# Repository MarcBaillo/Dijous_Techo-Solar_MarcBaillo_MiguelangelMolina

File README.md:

## Dijous_Techo-Solar_MarcBaillo_MiguelangelMolina
Proyecto de Herramientas de Diseño del Techo Solar (Jueves).

# Autores
- Miguelangel Molina(@MiaMoSaN)
- Marc Baillo (@MarcBaillo)

## Objectivos del proyecto

El objetivo que tenemos es conseguir diseñar un techo solar que estara formado por un microcontrolador, 2 motores que controlaran la apertura con final de carrera y el movimiento de la cortina, un sensor que evite atrapamientos y una luz ambiental producida por un LED RGB. Todo esto estara implementado en una PCB, pasando por las fases de diagrama de bloque, que luego pasar al esquematico y alfinal al layout, para luego evaluarlo y hacer unos presupuestos de cuanto valdra crear la placa.

## Requisitos i especificaciones:

- Diseño integral de un techo solar controlado por microcontrolador.
- Implementación de un motor de apertura con final de carrera.
- Integración de un motor de la cortina.
- Luz ambiental RGB.
- Integración de un sensor digital para evitar que atrapamientos.

## Diagrama de bloque

## Tabla de componentes
| Descripción        | Manufacturer Number          | Descripción | Datasheet          | Proveidor        | Unidades       | Precio Unitario |
|:----------------:|:-------------------------:|:----------------:|:---------------:|:--------------:|:--------------:|:--------------:|
| Microcontrolador | PIC18LF2580-I/SO | Procesador que actúa como cerebro de control del circuito | [Datasheet](https://ww1.microchip.com/downloads/aemDocuments/documents/OTH/ProductDocuments/DataSheets/39637d.pdf) | DigiKey | 1 | 9,2€ |
| Regulador de tensión | LM1117DT-3.3/NOPB  | Dispositivo que hace que la tensión de entrada pase de 12V a los que necesita el microcontrolador (3,3V) | [Datasheet](https://www.ti.com/lit/ds/symlink/lm1117.pdf?ts=1710745623625&ref_url=https%253A%252F%252Fwww.mouser.se%252F) | Mouser Electronics | 1 | 1,61€ |
| Conector | DB9  | Se ocupa de la conexión entre diferentes dispositivos |[Datasheet](https://www.mouser.es/datasheet/2/18/1/Cable_Glands_and_Cord_Grips-806485.pdf) | Mouser Electronics | 1 | 19,08€ |
| Oscilador | ECS-80-8-30-JGN-TR | Genera ondas de señales precisas| [Datasheet](https://www.mouser.es/datasheet/2/122/ecx_53r-1775695.pdf) | Mouser Electronics | 1 | 0,53€ |
| H-Driver | DRV8231ADDAR  | controla el sentido de giro de un motor | [Datasheet](https://www.ti.com/lit/ds/symlink/drv8231a.pdf?ts=1710753914026&ref_url=https%253A%252F%252Fwww.mouser.de%252F) | Mouser Electronics | 1 | 1,24€ |
| Transceiver | 	TCAN332DR  | Dispositivo que recibe y trtransmite datos |[Datasheet](https://www.ti.com/lit/ds/symlink/tcan332g.pdf?ts=1710924087476&ref_url=https%253A%252F%252Fwww.mouser.de%252F) | DigiKey | 1 | 2,83€ |
| LED RGB | LB Q39G-N1OO-35-1-5-R18  | LED que da luz ambiental al coche |[Datasheet](https://look.ams-osram.com/m/6e36864d019f51d4/original/LB-Q39G.pdf) | DigiKey | 1 | 0,2€ |
| Motor | D4387-12-ME  | Motores para poder abrir y cerrar el cristal o la cortina del techo | [Datasheet](https://transmotec.es/Download/Catalog/Transmotec-EN-DC-12W-450W-2022.pdf) | Transmotec | 2 | 345€ |
| Switch | SS-01GPD  | Dispositivos que controlan cuando es el final de carrera | [Datasheet](https://www.mouser.es/datasheet/2/307/en_ss-1509069.pdf) | Mouser Electronics | 1 | 1,27€ |
| Pulsador | MPB01-1B00-S-D  | Dispositivo que permite controlar el motor para que el techo o cortina se abra o se cierre  | [Datasheet](https://www.mouser.es/datasheet/2/670/mpb01-2474754.pdf) | Mouser Electronics | 2 | 3,14€ |
| Conector | ICSP  | Sirve para comunicarse con el exterior para programar el microcontrolador | [Datasheet](https://ww1.microchip.com/downloads/en/DeviceDoc/30277d.pdf) | DigiKey | 2 | 1,52€ |

## Historial de canvis 

| Data | Autor | Descripció |
|:------:|:------:|:------------:|
| 20-03-2025 | Marc y Miguel | Creado el proyecto y escogido el diseño que se trabajara (Techo Solar) |
| 20-03-2025 | Marc y Miguel | Elección de componentes y presentación del proyecto (Sesión 1) |
| 20-03-2025 | Marc y Miguel | Creación de Diagrama de Bloque |
| 23-03-2025 | Marc | Cadlab y GitHub creado |
| 24-03-2025 | Miguel | Creación del Esquematico |
| 25-03-2025 | Marc | Simulaciones hechas |
| 26-03-2025 | Miguel | Modificación Diagrama de Bloque |
| 27-03-2025 | Marc | Creació del README |
| 27-03-2025 | Marc y Miguel | Modificación presentación proyecto (Sesión 2) |
| 31-03-2025 | Miguel | Creación Layout |
| 02-04-2025 | Marc | Simulación ADC hecha |
| 03-04-2025 | Miguel y Marc | Modificación presentación proyecto (Sesión 3) |
| 03-04-2025 | Miguel | Corrección errores Layout y Esquematicos |
| 09-04-2025 | Marc | Modificación Layout (acabar de poner vista 3D y packages bien) |
| 09-04-2025 | Marc |  Modificación presentación proyecto (Sesión 4)  |
| 10-04-2025 | Marc y Miguel |  Modificación presentación proyecto (Sesión 4)  |
| 10-04-2025 | Miguel | Finalización del Esquematico y del Layout |
| 10-04-2025 | Miguel | Reglas de diseño definidas |
| 23-04-2025 | Marc | Presupuesto hecho |
| 24-04-2025 | Miguel y Marc | Modificación presentación proyecto (Sesión presentación proyecto final) |

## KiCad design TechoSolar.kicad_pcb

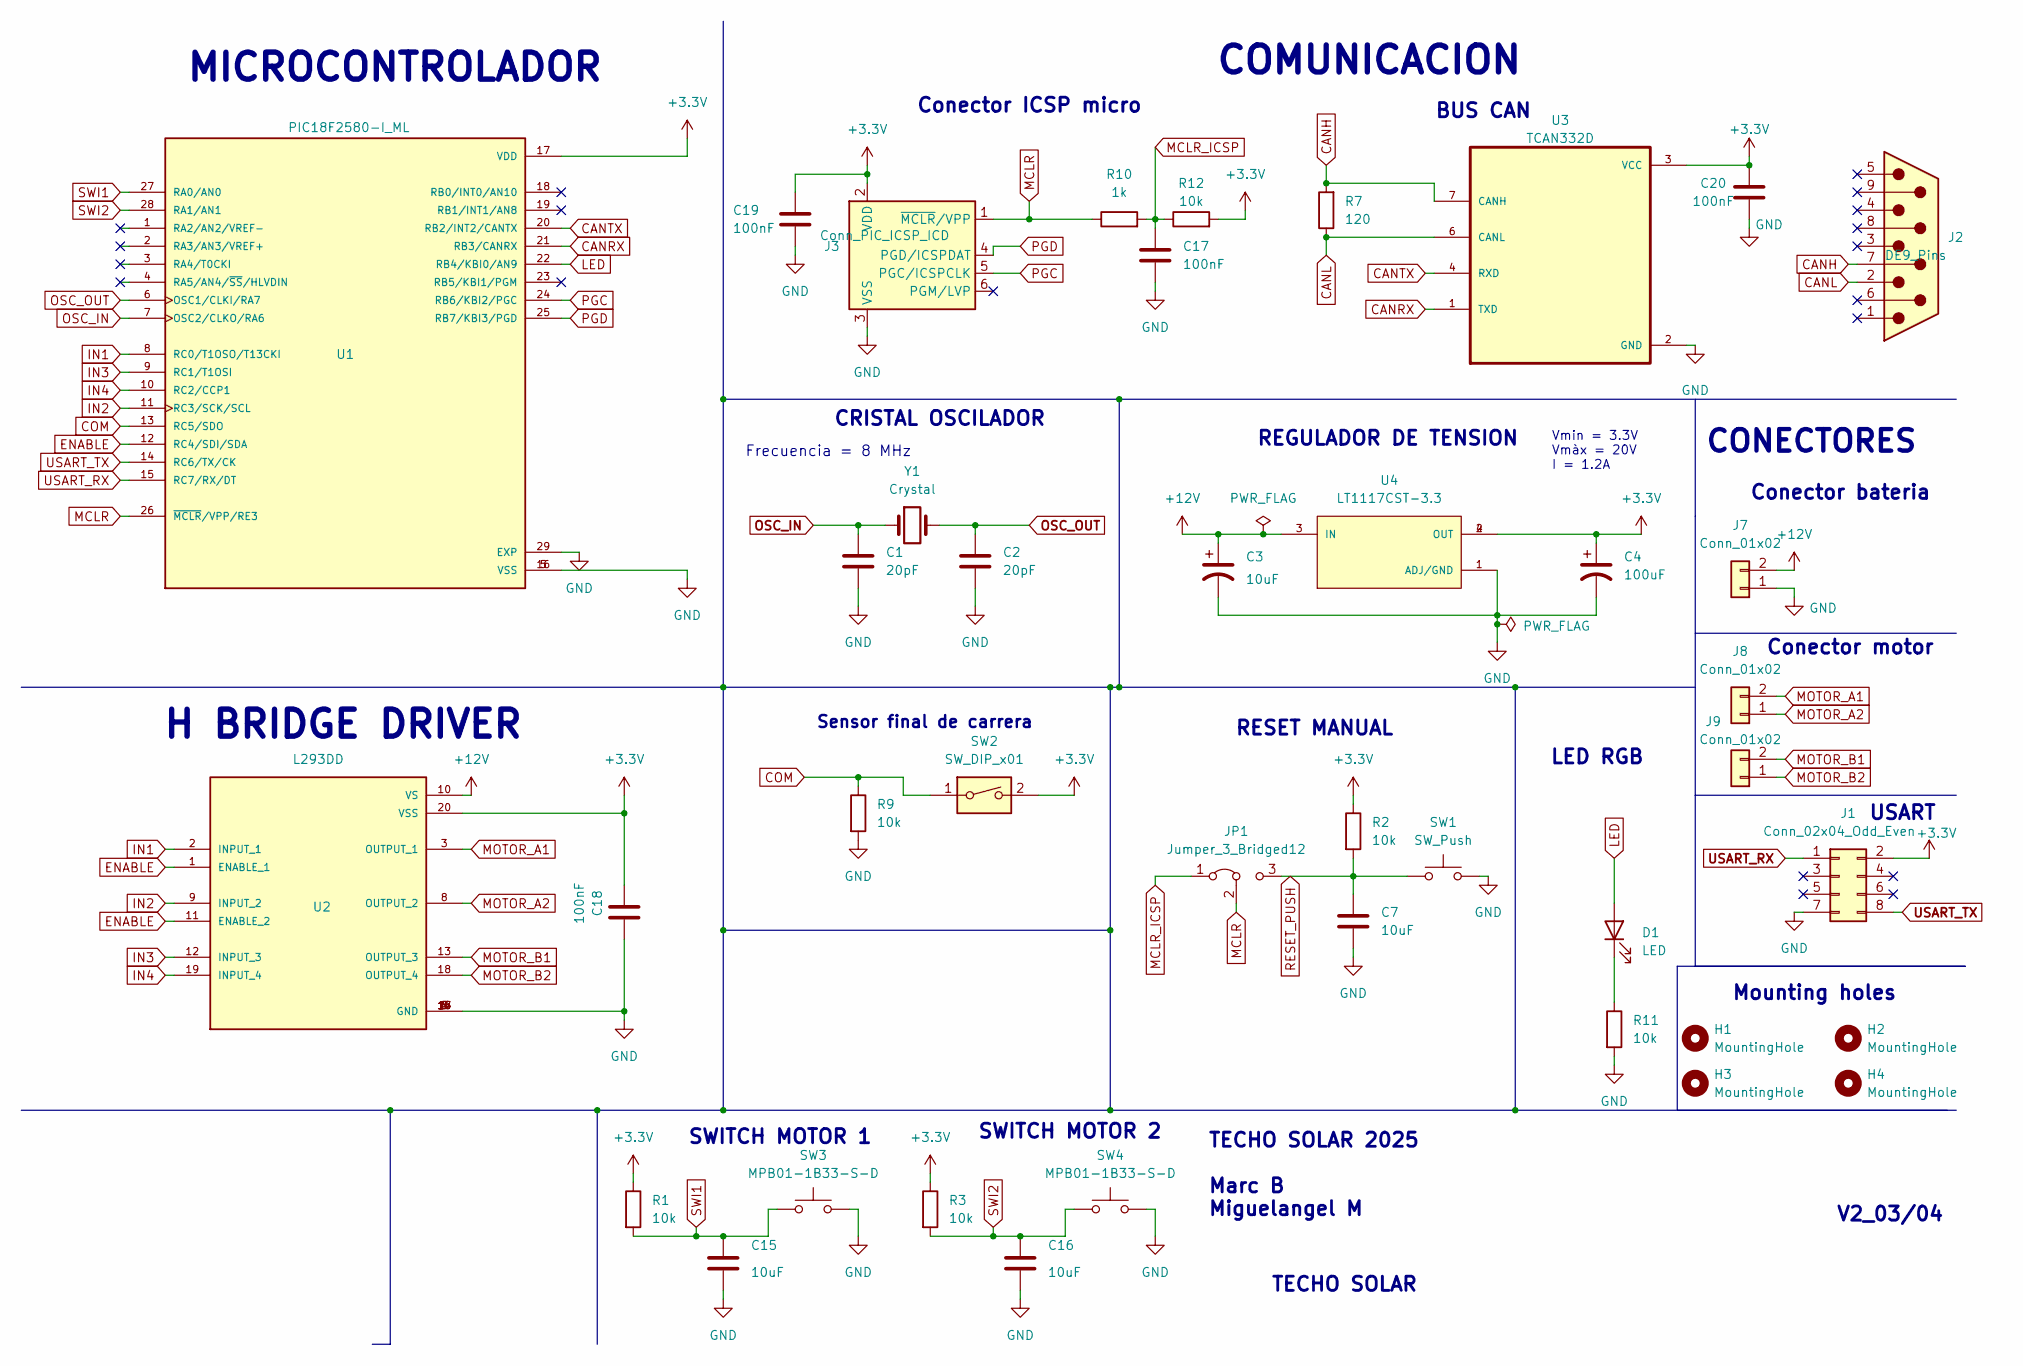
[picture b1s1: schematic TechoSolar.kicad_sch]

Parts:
C1, C2: 20pF; C_0805_2012Metric_Pad1.18x1.45mm_HandSolder
C3, C7, C15, C16: 10uF; C_0805_2012Metric_Pad1.18x1.45mm_HandSolder
C4: 100uF; C_0805_2012Metric_Pad1.18x1.45mm_HandSolder
C17, C18, C19, C20: 100nF; C_0603_1608Metric_Pad1.08x0.95mm_HandSolder
D1: LED; LED_0603_1608Metric
H1, H2, H3, H4: MountingHole; MountingHole_3.2mm_M3
J1: Conn_02x04_Odd_Even; PinHeader_2x04_P2.54mm_Vertical
J2: DE9_Pins; DB9
J3: Conn_PIC_ICSP_ICD; PinSocket_1x06_P2.54mm_Vertical
J7, J8, J9: Conn_01x02; PinHeader_1x02_P2.54mm_Vertical
JP1: Jumper_3_Bridged12; PinHeader_1x03_P2.54mm_Vertical
R1, R2, R3, R9, R11, R12: 10k; R_0805_2012Metric_Pad1.20x1.40mm_HandSolder
R7: 120; R_0805_2012Metric_Pad1.20x1.40mm_HandSolder
R10: 1k; R_0805_2012Metric_Pad1.20x1.40mm_HandSolder
SW1: SW_Push; SW_PUSH_6mm
SW2: SW_DIP_x01; SW_DIP_SPSTx01_Slide_6.7x4.1mm_W7.62mm_P2.54mm_LowProfile
SW3, SW4: MPB01-1B33-S-D; SW_PUSH_6mm
U1: PIC18F2580-I_ML; QFN65P600X600X100-29N; PARTREV D
U2: L293DD; SOIC127P1032X265-20N; PARTREV N/A
U3: TCAN332D; SOIC127P599X175-8N
U4: LT1117CST-3.3; REG_LT1117CST-3.3
Y1: Crystal; ECS80830JGNTR

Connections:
+3.3V: C4.1, C18.2, C19.1, C20.2, J1.2, J3.2 (VDD), R1.1, R2.1, R3.1, R12.2, SW2.2, U1.17 (VDD), U2.20 (VSS), U3.3 (VCC), U4.2 (OUT), U4.4 (OUT); also elsewhere on the board
+12V: C3.1, J7.2, U2.10 (VS), U4.3 (IN)
CANH: J2.7, R7.2, U3.7 (CANH)
CANL: J2.2, R7.1, U3.6 (CANL)
CANRX: U1.21 (RB3/CANRX), U3.1 (TXD)
CANTX: U1.20 (RB2/INT2/CANTX), U3.4 (RXD)
COM: R9.1, SW2.1, U1.13 (RC5/SDO)
ENABLE: U1.12 (RC4/SDI/SDA), U2.1 (ENABLE_1), U2.11 (ENABLE_2)
GND: C1.2, C2.2, C3.2, C4.2, C7.2, C15.2, C16.2, C17.2, C18.1, C19.2, C20.1, J1.7, J3.3 (VSS), J7.1, R9.2, R11.2, SW1.2, SW3.2, SW4.2, U1.5 (VSS), U1.16 (VSS), U1.29 (EXP), U2.4 (GND), U2.5 (GND), U2.6 (GND), U2.7 (GND), U2.14 (GND), U2.15 (GND), U2.16 (GND), U2.17 (GND), U3.2 (GND), U4.1 (ADJ/GND); also elsewhere on the board
IN1: U1.8 (RC0/T1OSO/T13CKI), U2.2 (INPUT_1)
IN2: U1.11 (RC3/SCK/SCL), U2.9 (INPUT_2)
IN3: U1.9 (RC1/T1OSI), U2.12 (INPUT_3)
IN4: U1.10 (RC2/CCP1), U2.19 (INPUT_4)
LED: D1.2 (A), U1.22 (RB4/KBI0/AN9)
MCLR: J3.1 (~MCLR/VPP), JP1.2 (C), R10.1, U1.26 (~MCLR/VPP/RE3)
MCLR_ICSP: C17.1, JP1.1 (A), R10.2, R12.1
MOTOR_A1: J8.2, U2.3 (OUTPUT_1)
MOTOR_A2: J8.1, U2.8 (OUTPUT_2)
MOTOR_B1: J9.2, U2.13 (OUTPUT_3)
MOTOR_B2: J9.1, U2.18 (OUTPUT_4)
unnamed: D1.1 (K), R11.1
OSC_IN: C1.1, U1.7 (OSC2/CLKO/RA6), Y1.1
OSC_OUT: C2.1, U1.6 (OSC1/CLKI/RA7), Y1.2
PGC: J3.5 (PGC/ICSPCLK), U1.24 (RB6/KBI2/PGC)
PGD: J3.4 (PGD/ICSPDAT), U1.25 (RB7/KBI3/PGD)
RESET_PUSH: C7.1, JP1.3 (B), R2.2, SW1.1
SWI1: C15.1, R1.2, SW3.1, U1.27 (RA0/AN0)
SWI2: C16.1, R3.2, SW4.1, U1.28 (RA1/AN1)
USART_RX: J1.1, U1.15 (RC7/RX/DT)
USART_TX: J1.8, U1.14 (RC6/TX/CK)

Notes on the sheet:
V2_03/04
BUS CAN
Vmin = 3.3V Vmàx = 20V I = 1.2A
MICROCONTROLADOR
COMUNICACION
TECHO SOLAR
SWITCH MOTOR 1
LED RGB
CRISTAL OSCILADOR
Frecuencia = 8 MHz
CONECTORES
RESET MANUAL
SWITCH MOTOR 2
TECHO SOLAR 2025 Marc B Miguelangel M
Conector bateria
Conector ICSP micro
Sensor final de carrera
Conector motor
H BRIDGE DRIVER
REGULADOR DE TENSION
USART
Mounting holes

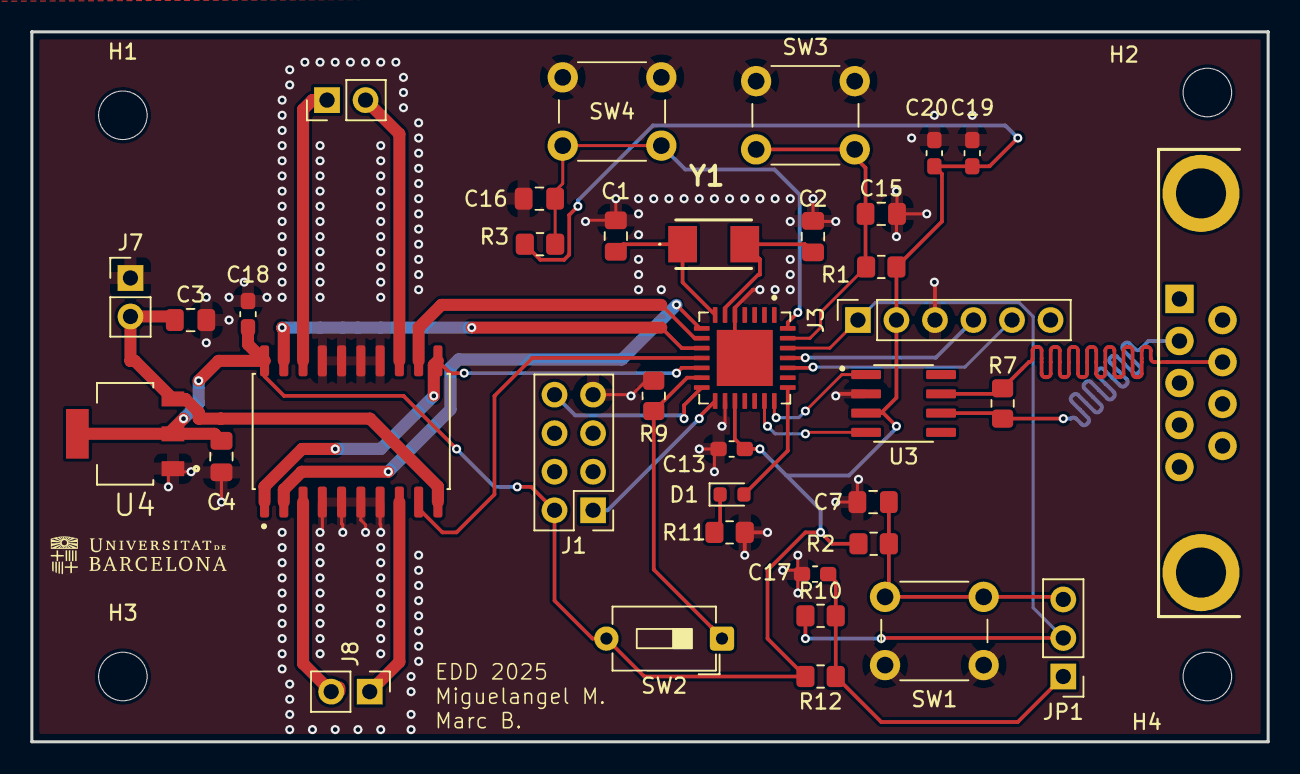
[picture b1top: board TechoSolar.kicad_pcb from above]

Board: 2 copper layers, 81.5 x 46.8 mm, 41 parts (0 on the bottom side), 30 nets.

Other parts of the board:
C13: 100nF; C_0603_1608Metric_Pad1.08x0.95mm_HandSolder

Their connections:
+3.3V: C13.2; also elsewhere on the board
GND: C13.1; also elsewhere on the board

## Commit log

2025-03-23 Create Prueba 1
2025-03-23 Backlink to CADLAB.io has been added.
2025-03-23 Create Prueba 2
2025-03-23 Elimino estos 2 archivos de prubea README
2025-03-27 README actualizado
2025-03-27 Actualizacion del REadme 2
2025-03-27 Actualizacion readme 3
2025-03-27 Actualizacion readme 4
2025-03-27 actualizacion readme 5
2025-03-27 actualizacion readme 6
2025-03-27 Poniendo lo nuevo
2025-03-27 actulizacion Bloque Diagrama en Readme
2025-03-27 otra prueba
2025-03-27 actu
2025-03-27 Actualizacion
2025-03-27 Presentaciones
2025-03-27 README nuevo
2025-03-27 Create prueba
2025-03-27 Create 2a prueba
2025-03-27 Upload Esquematico_TechoSolar
2025-04-02 Añadiendo Layout circuito
2025-04-02 Actualización README y importación simulaciones
2025-04-02 REadme ajuste
2025-04-03 Simulacion de opamp
2025-04-03 PResentacion dia 3
2025-04-03 Actualización README
2025-04-09 Actualizacion REadme
2025-04-10 Sesion 4 modificaciones
2025-04-10 Create Reglas de Diseño
2025-06-05 Upload TECHO SOLAR_VersiónFinal_24_04.pdf
